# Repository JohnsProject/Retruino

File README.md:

# Retruino
Retruino is a tiny retro gaming console for the arduino, it's based on the , what enables you to upload multiple retro games once and play them.
## Creating your own games
It's very simple to create your own Retruino games. 

First you need to download the repository, with that done, open the ``Retruino.ino`` file with the Arduino IDE. Now add a new file to the sketch called ``TestGame.h``.

This game will be about moving a rectangle on the display using the joystick.

And here is how it looks like

```C++
#ifndef __TESTGAME_H__
#define __TESTGAME_H__

#include "Retruino.h"

class TestGame: public App {

    const uint32_t BLACK = 0x0;
    const uint32_t WHITE = 0xffffff;

    uint8_t position_x;
    uint8_t position_y;
    const uint8_t SIZE = 5;

    String getName() {
      // return name of the game
      return "TestGame";
    }

    void setup() {
      // fill display black
      display.fill(BLACK);
      // set start position at the center of the display
      position_x = display.HALF_WIDTH;
      position_y = display.HALF_HEIGHT;
    }

    void loop() {
      // erase old rectangle
      display.fillRect(position_x, position_y, SIZE, SIZE, BLACK);
      // update position based on joystick position
      position_x += input.readJoystickDirection(input.JOY_X);
      position_y += input.readJoystickDirection(input.JOY_Y);
      // draw rectangle at new position
      display.fillRect(position_x, position_y, SIZE, SIZE, WHITE);
      delay(16);
    }
    
} testGame;

#endif
```

To finish you need to add your app to the kernel, to do so add ``#include "TestGame.h"`` and ``kernel.addApp(testGame)`` to the ``Retruino.ino`` file.

Congrats! you've just created your first Retruino app.

## NOTE: The Retruino needs the Arduios library installed in your Arduino IDE.

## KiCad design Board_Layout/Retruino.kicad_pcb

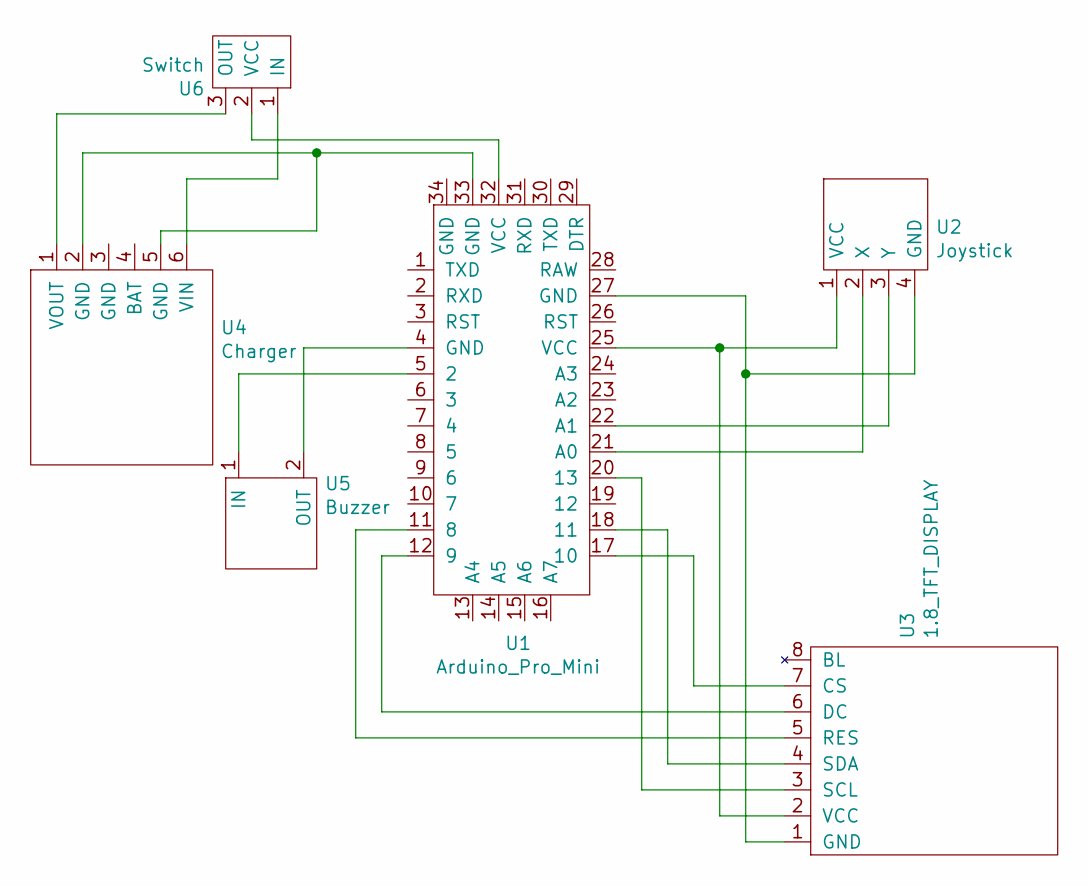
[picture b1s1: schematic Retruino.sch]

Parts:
U1: Arduino_Pro_Mini; Arduino_pro_mini
U2: Joystick
U3: 1.8_TFT_DISPLAY; 1.8_TFT_Display
U4: Charger
U5: Buzzer
U6: Switch

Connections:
unnamed: U1.4 (GND), U5.2 (OUT)
unnamed: U1.5 (2), U5.1 (IN)
unnamed: U1.11 (8), U3.5 (RES)
unnamed: U1.12 (9), U3.6 (DC)
unnamed: U1.17 (10), U3.7 (CS)
unnamed: U1.18 (11), U3.4 (SDA)
unnamed: U1.20 (13), U3.3 (SCL)
unnamed: U1.21 (A0), U2.2 (X)
unnamed: U1.22 (A1), U2.3 (Y)
unnamed: U1.25 (VCC), U2.1 (VCC), U3.2 (VCC)
unnamed: U1.27 (GND), U2.4 (GND), U3.1 (GND)
unnamed: U1.32 (VCC), U6.2 (VCC)
unnamed: U1.33 (GND), U4.2 (GND), U4.5 (GND)
unnamed: U4.1 (VOUT), U6.3 (OUT)
unnamed: U4.6 (VIN), U6.1 (IN)

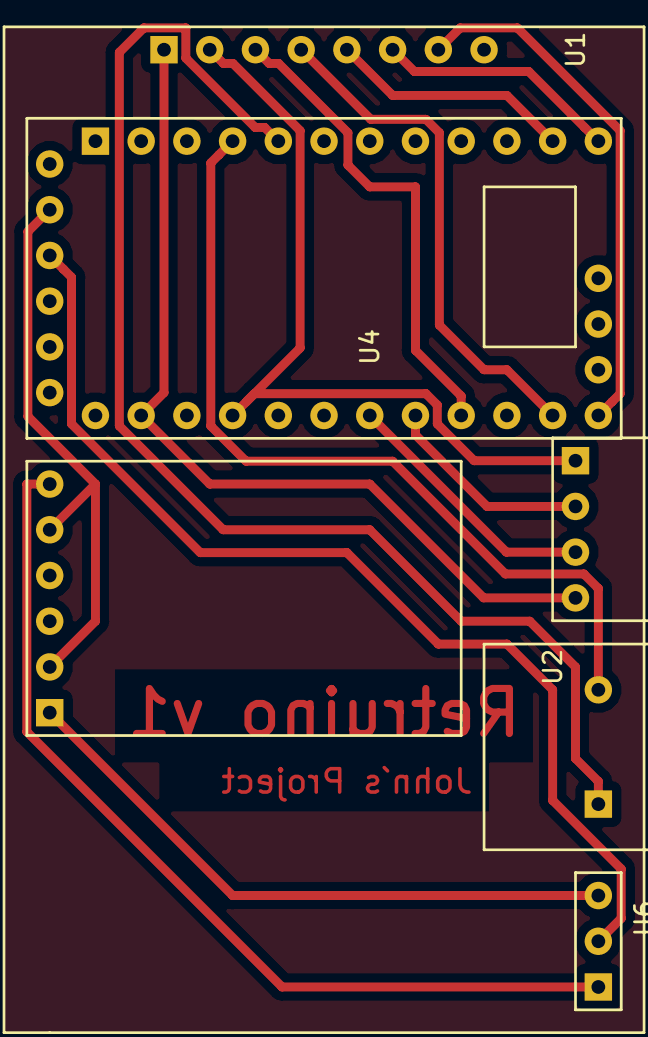
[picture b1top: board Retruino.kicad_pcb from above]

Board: 2 copper layers, 6 parts (0 on the bottom side), 15 nets.

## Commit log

2019-06-12 Refactored
